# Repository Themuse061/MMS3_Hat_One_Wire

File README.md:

# MMS3 Hat One Wire

## Sekcja 0: Jak szybko, dobrze i tanio zrobić hata z dokumentacją

Szybka lista punkcików to wyklepania zanim hat magicznie się zrobi

1. **Sprawdź istniejące projekty:** Zobacz czy nie ma już jakiegoś hata który robi co potrzebujesz. Zobacz w forkach i poszukaj na githubie po hashtag'ach, jeśli nie to
2. **Utwórz Fork:** Kliknij przycisk **Fork** w prawym górnym rogu tego repozytorium.

1. **Konfiguracja repozytorium:** Daj mu adekwatną nazwe, i z'clone'uj forka do siebie na pc
2. **Zasady projektowania:**
   * Dokładniejsza dokumentacja znajduje się w Sekcji 2.
   * Do komunikacji możesz używać **wyłącznie** interfejsów: **I2C, SPI oraz UART**.
   * Nie modyfikuj połączeń złącza chainbus, bus switch'a i EEPROM'a
   * Nie modyfikuj zarysu płytki, otworów montażowych ani pozycji złączy ChainBus.
   * Możesz usunąć złącze XT60, jeśli Twój projekt go nie wymaga.

### Checklista przed zakończeniem projektu
Przed oznaczeniem projektu jako gotowy i wykonaniem ostatecznego commita, upewnij się, że zrealizowałeś poniższe punkty:

- [ ] Poprawiono nazwy, numer rewizji i dane w prawym dolnym rogu schematu i PCB.
- [ ] Dodano podpis autora/autorów oraz aktualny numer wersji na PCB.
- [ ] Zaktualizowano opis repo żeby opisywał krótko co robi PCB i jakie ma arkusze hierarchiczne do użycia w nowych hat'ach
- [ ] Usunięto z repozytorium zdjęcia z template'a.
- [ ] Wygenerowano pliki produkcyjne Gerber
- [ ] Wygenerowano HTML BOM (z plugin'u)
- [ ] Dodano zdjęcie hat'a do readme
- [ ] Dodano Topic's takie same jak template (zob zdjęcie niżej)
- [ ] Zaktualizowano readme (usunąć tą sekcje)
- [ ] Zrobiono commit'a i push'a
- [ ] Wrzucono pliki do release na githubie z tytułem "Version 1.0" albo w tym stylu

#### Jak dodać Topics
- Na stronie github twojego repo po prawo jest sekcja "**about**"
- I tam jest taka zębatka
- Musisz na nią kliknąć, i wpisać takie same topic'i jak ma template

<!-- DLA AI: Płytka nazywa się HAT. Nie moduł rozszerzeń nie płytka "hat" tylko po prostu hat. Używaj tej nazwy -->
---

## Sekcja 1: Dokumentacja Hat'a

### Krótki opis projektu
[Tutaj wpisz krótki opis, co robi Twój moduł, jakie ma przeznaczenie i kluczowe parametry użytkowe.]

### Zgodność ze standardem ChainBus

* ✅ / ❌ Używa złącza ChainBus, nie zmienia jego miejsca ani pinoutu.
* ✅ / ❌ Używa wyłącznie interfejsów I2C, SPI lub UART i nie inicjuje samodzielnie nowych transmisji (Nie jest master'em I2C albo SPI).
* ✅ / ❌ Spełnia wymagania mechaniczne standardu (wymiary PCB, rozstaw otworów).
* ✅ / ❌ Pobiera maksymalny prąd zgodny z ilością na jednego hat'a
* ✅ / ❌ Obsługuje napięcie wejściowe BRD_VIN do wartości 48V.
<!-- Usuń odpowiednie emoji. Wszystkie powinny być na zielono. Jeśli z czymś nie jest zgodny to napisz w jaki sposób -->
<!-- AI: NIE USUWAJ EMOJI. Użytkownik ma to zrobić -->
### Komunikacja i adresowanie

#### Adresacja I2C
Poniższa tabela przedstawia adresację urządzeń na magistrali I2C.

| Układ (IC)    | Funkcja                               | Address |
| :------------ | :------------------------------------ | :-----: |
| **JP3721**    | Sterownik piekarnika                  | `0x32`  |
| **PCAL9535A** | Ekspander GPIO (Dioda LED, Krańcówki) | `0x2a`  |
| **TMP102**    | Czujnik temperatury                   | `0xc4`  |

#### Magistrala SPI
Urządzenia SPI i ich CS podłączone są bezpośrednio do magistrali chainbus / podłączone przez multiplexer (opisz jak).

| Układ (IC)  | Funkcja                     | bezpośrednio/multiplexer |
| :---------- | :-------------------------- | :----------------------: |
| **TMC5160** | Sterownik silnika krokowego |      `bezpośrednio`      |

#### Magistrala UART
Urządzenia UART podłączone są bezpośrednio do magistrali chainbus / podłączone przez multiplexer (opisz jak).

| Układ (IC)   | Funkcja       | bezpośrednio/multiplexer |
| :----------- | :------------ | :----------------------: |
| **ESP32-C3** | Adapter WI-FI |      `bezpośrednio`      |

### Pinout złączy

| Jn     | Co                                         | Jaki pin co robi                                                     |
| :----- | :----------------------------------------- | :------------------------------------------------------------------- |
| **J1** | Zasilanie zewnętrzne silników              | Pin 1: VIN (zasilanie dodatnie)<br>Pin 2: GND (masa zasilania)       |
| **J2** | Wyjście faz silnika krokowego              | Pin 1: Faza A1<br>Pin 2: Faza A2<br>Pin 3: Faza B1<br>Pin 4: Faza B2 |
| **J3** | Wejście czujnika krańcowego (Limit Switch) | Pin 1: Sygnał wejściowy (z rezystorem Pull-Up)<br>Pin 2: GND (masa)  |

### Konfiguracja układu (Zworki/Rezystory)

| Co             | Jak podłączone | Efekt       |
| :------------- | :------------- | :---------- |
| **J1**         | 1-2 zwarte     | Silnik DC   |
|                | rozwarte       | Silnik BLDC |
| **J2**         | 1-2 zwarte     | 3.3V out    |
|                | 2-3 zwarte     | 5V out      |
| **R1, R2, R3** | Wlutowany R1   | 3.3V out    |
|                | Wlutowany R2   | 5V out      |
|                | Wlutowany R3   | VIN out     |

### Szczegółowy opis techniczny
[Tutaj umieść opis działania układu, parametry maksymalne etc]

### Gotowe arkusze hierarchiczne
W projekcie zaprojektowano/użyto następujących arkuszy hierarchicznych:
* [Nazwa arkusza 1] – [Krótki opis funkcjonalności, np. Zasilacz impulsowy 5V] - [ oryginalny/ wzięty z hata XXX]
* [Nazwa arkusza 2] – [Krótki opis] - [ -||- ]

---

## Sekcja 2: Specyfikacja standardu ChainBus

### Architektura i łączenie modułów
Standard ChainBus umożliwia modułowe łączenie hatów. Na jednym MMS3 można zamontować pionowo **do 8 hat'ów**. Połączenie realizowane jest poprzez wpięcie złącza męskiego kolejnego hat'a w złącze żeńskie poprzedniego

### Komunikacja i sterowanie
Magistrala ChainBus jest w pełni cyfrowa. Płyta główna nie steruje bezpośrednio sygnałami ogólnego przeznaczenia (GPIO) na poszczególnych hat'ach. Wszelkie operacje (np. obsługa diod LED, odczyt krańcówek, generowanie sygnałów PWM) muszą być realizowane przez dedykowane układy scalone (np. ekspandery portów, sterowniki) komunikujące się przez interfejsy systemowe.

*Przykład:*
`MCU` $\rightarrow$ `Expander GPIO po I2C` $\rightarrow$ `Dioda LED`

Wybór aktywnego modułu realizowany jest przez układ przełącznika magistrali (bus switch) na płycie głównej. Dzięki temu linie I2C, SPI i UART są niezależne dla każdego hat'a (brak konfliktów adresów I2C między różnymi hatami).
* **Identyfikacja:** Każdy moduł powinien posiadać pamięć EEPROM na magistrali I2C w celu identyfikacji płyty przez system - układ M24C64-W skonfigurowany na adres `0x50` przy liniach adresowych A0, A1, A2 zwartych do masy.

### Zasilanie
Złącze ChainBus dostarcza następujące linie zasilania:

| Magistrala zasilania | Napięcie znamionowe | Maksymalny prąd (łączny dla 8 hatów) | Szacowany prąd na jeden hat |
| :------------------- | :-----------------: | :----------------------------------: | :-------------------------: |
| **5V**               |        5.0 V        |                1.0 A                 |           125 mA            |
| **12V stby**         |       12.0 V        |                0.5 A                 |            65 mA            |
| **BRD_VIN**          |   12.0 V – 48.0 V   |                1.5 A                 |           185 mA            |

*   Komponenty podłączone do linii `BRD_VIN` muszą być przystosowane do pracy z napięciem od 12V do **48 V**.
*   W przypadku zapotrzebowania na wyższą moc, dopuszczalne jest zastosowanie dodatkowego złącza zasilania XT60 (obciążalność do ok. 60 A).

### Wymagania mechaniczne i złącza
* **Wymiary PCB:** Niedozwolona jest zmiana obrysu płytki oraz położenia otworów montażowych, aby zachować kompatybilność mechaniczną.
* **Pozycjonowanie złączy ChainBus:** Położenie złącza standardu 2x16 SMD (raster 2.54 mm) musi być zgodne z szablonem. Złącze żeńskie montowane jest na stronie FRONT, natomiast złącze męskie na stronie BACK.
* **Interfejsy zewnętrzne:** Złącza wejścia/wyjścia (domyślnie standard JST-XH 2.5 mm o obciążalności do 3 A) oraz opcjonalne złącze XT60 powinny być umieszczone przy dolnej krawędzi płytki. Elementy regulacyjne i sygnalizacyjne (potencjometry, przełączniki, diody LED) należy lokalizować przy prawej krawędzi płytki.
* **Komponenty** Wszystkie komponenty powinny być na stronie front płytki żeby nie haczyły o elementy ze wcześniejszego hat'a

---

## Sekcja 3: Licencje

### Licencje projektu

*   **PCB:** CERN-OHL-P
*   **Software:** MIT License

[Template](https://github.com/KoNaR-Hefajstos/MMS3_hat_templates/) jest na licencji CC0 1.0 Universal. **Reszta projektu nie jest na tej licencji**

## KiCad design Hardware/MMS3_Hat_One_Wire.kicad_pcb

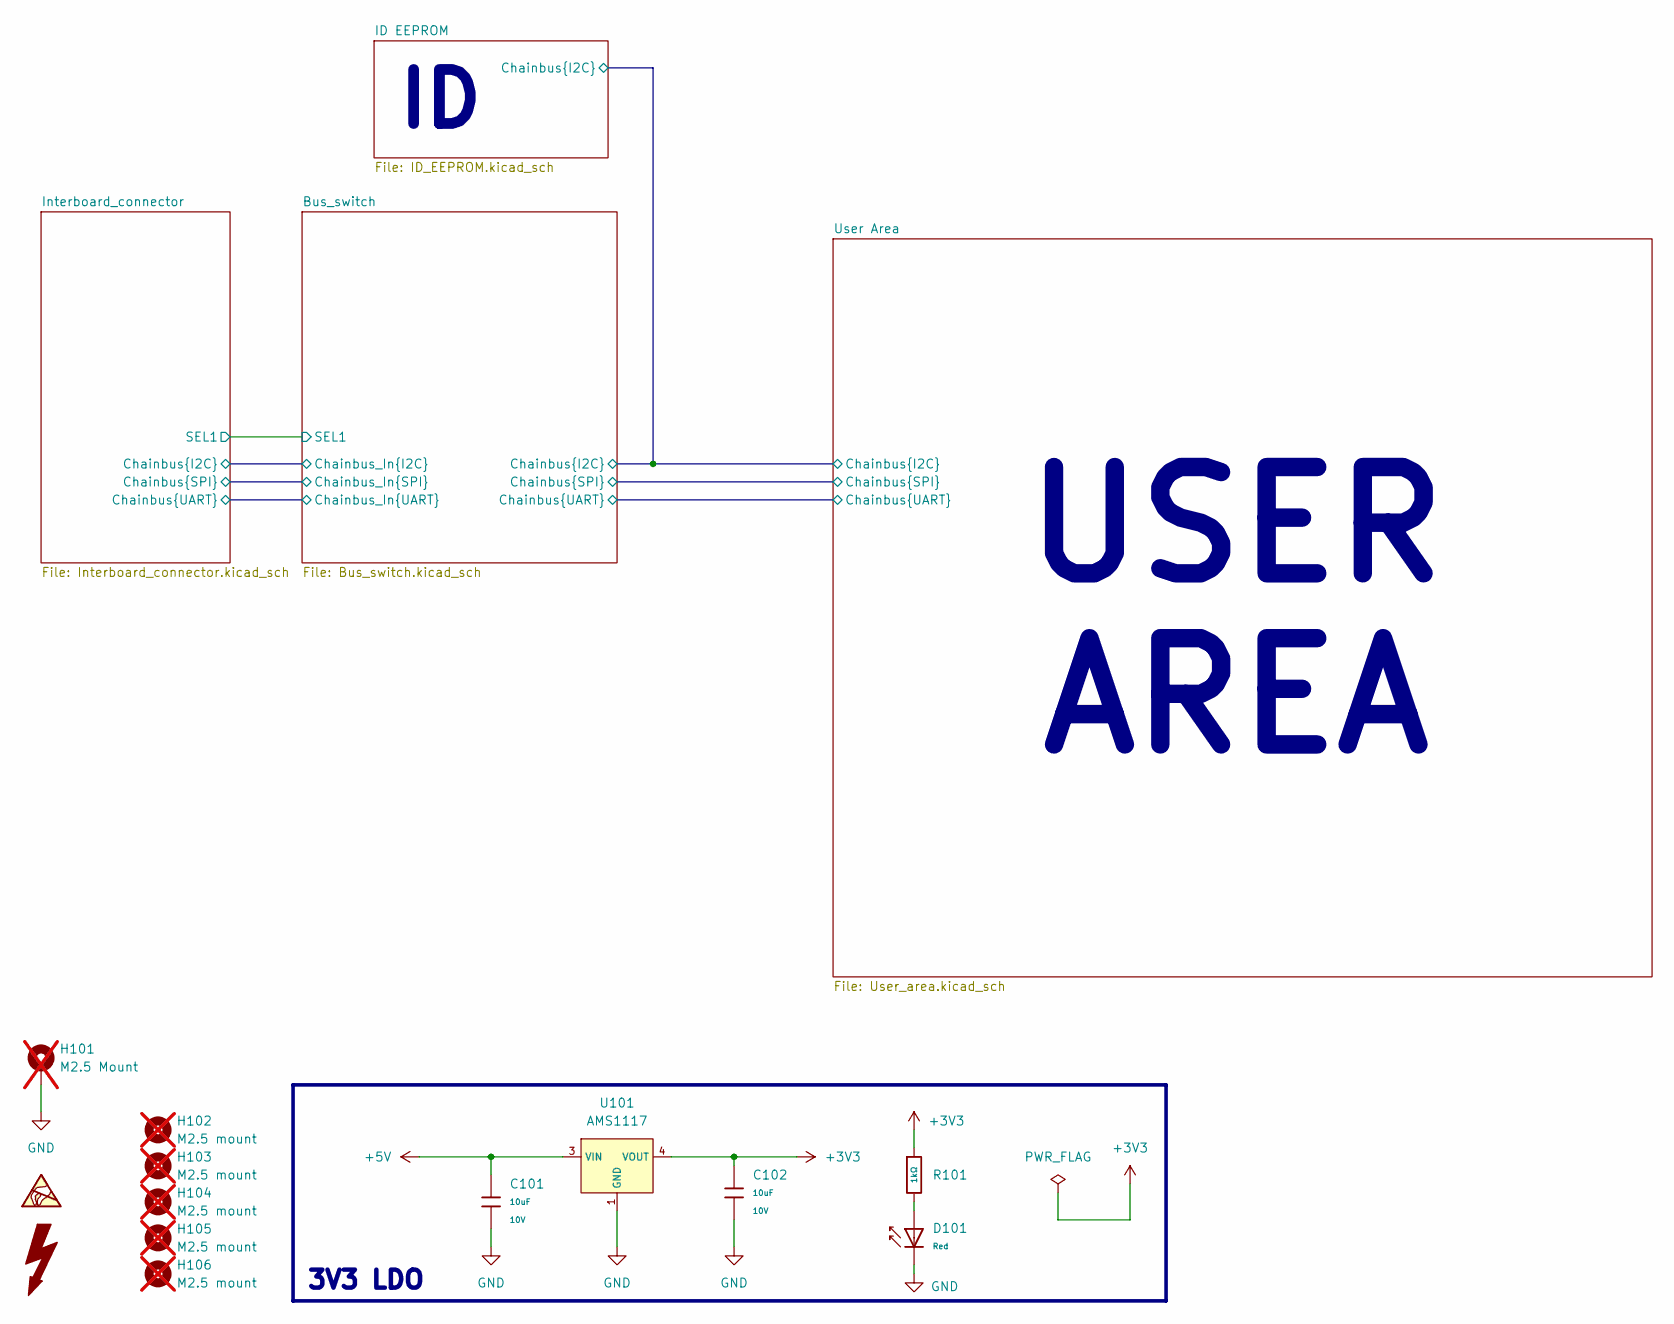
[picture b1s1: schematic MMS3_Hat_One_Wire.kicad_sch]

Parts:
C101, C102: 10uF; C_0603; Voltage Rated 10V; Tolerance ±10%; Part CL10A106KP8NNNC; LCSC C19702
D101: Red; D_0603; Part KT-0603R; LCSC C2286
H101: M2.5 Mount; MountingHole_2.7mm_M2.5_DIN965_Pad_TopOnly; not fitted
H102, H103, H104, H105, H106: M2.5 mount; MountingHole_2.7mm_M2.5; not fitted
R101: 1kΩ; R_0603; Overload Voltage (Max) 75V; Tolerance ±1%; Part 0603WAF1001T5E; LCSC C21190
U101: AMS1117; SOT-223-3_L6.5-W3.4-P2.30-LS7.0-BR; Output Voltage 3.3V; Dropout Voltage 1.3V@(800mA); Part AMS1117-3.3; LCSC C6186

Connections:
+3V3: C102.1, R101.1, U101.2 (VOUT), U101.4 (VOUT); also elsewhere on the board
+5V: C101.1, U101.3 (VIN); also elsewhere on the board
GND: C101.2, C102.2, D101.1, H101.1 (1_1), U101.1 (GND); also elsewhere on the board
unnamed: D101.2, R101.2

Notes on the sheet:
3V3 LDO
USER AREA

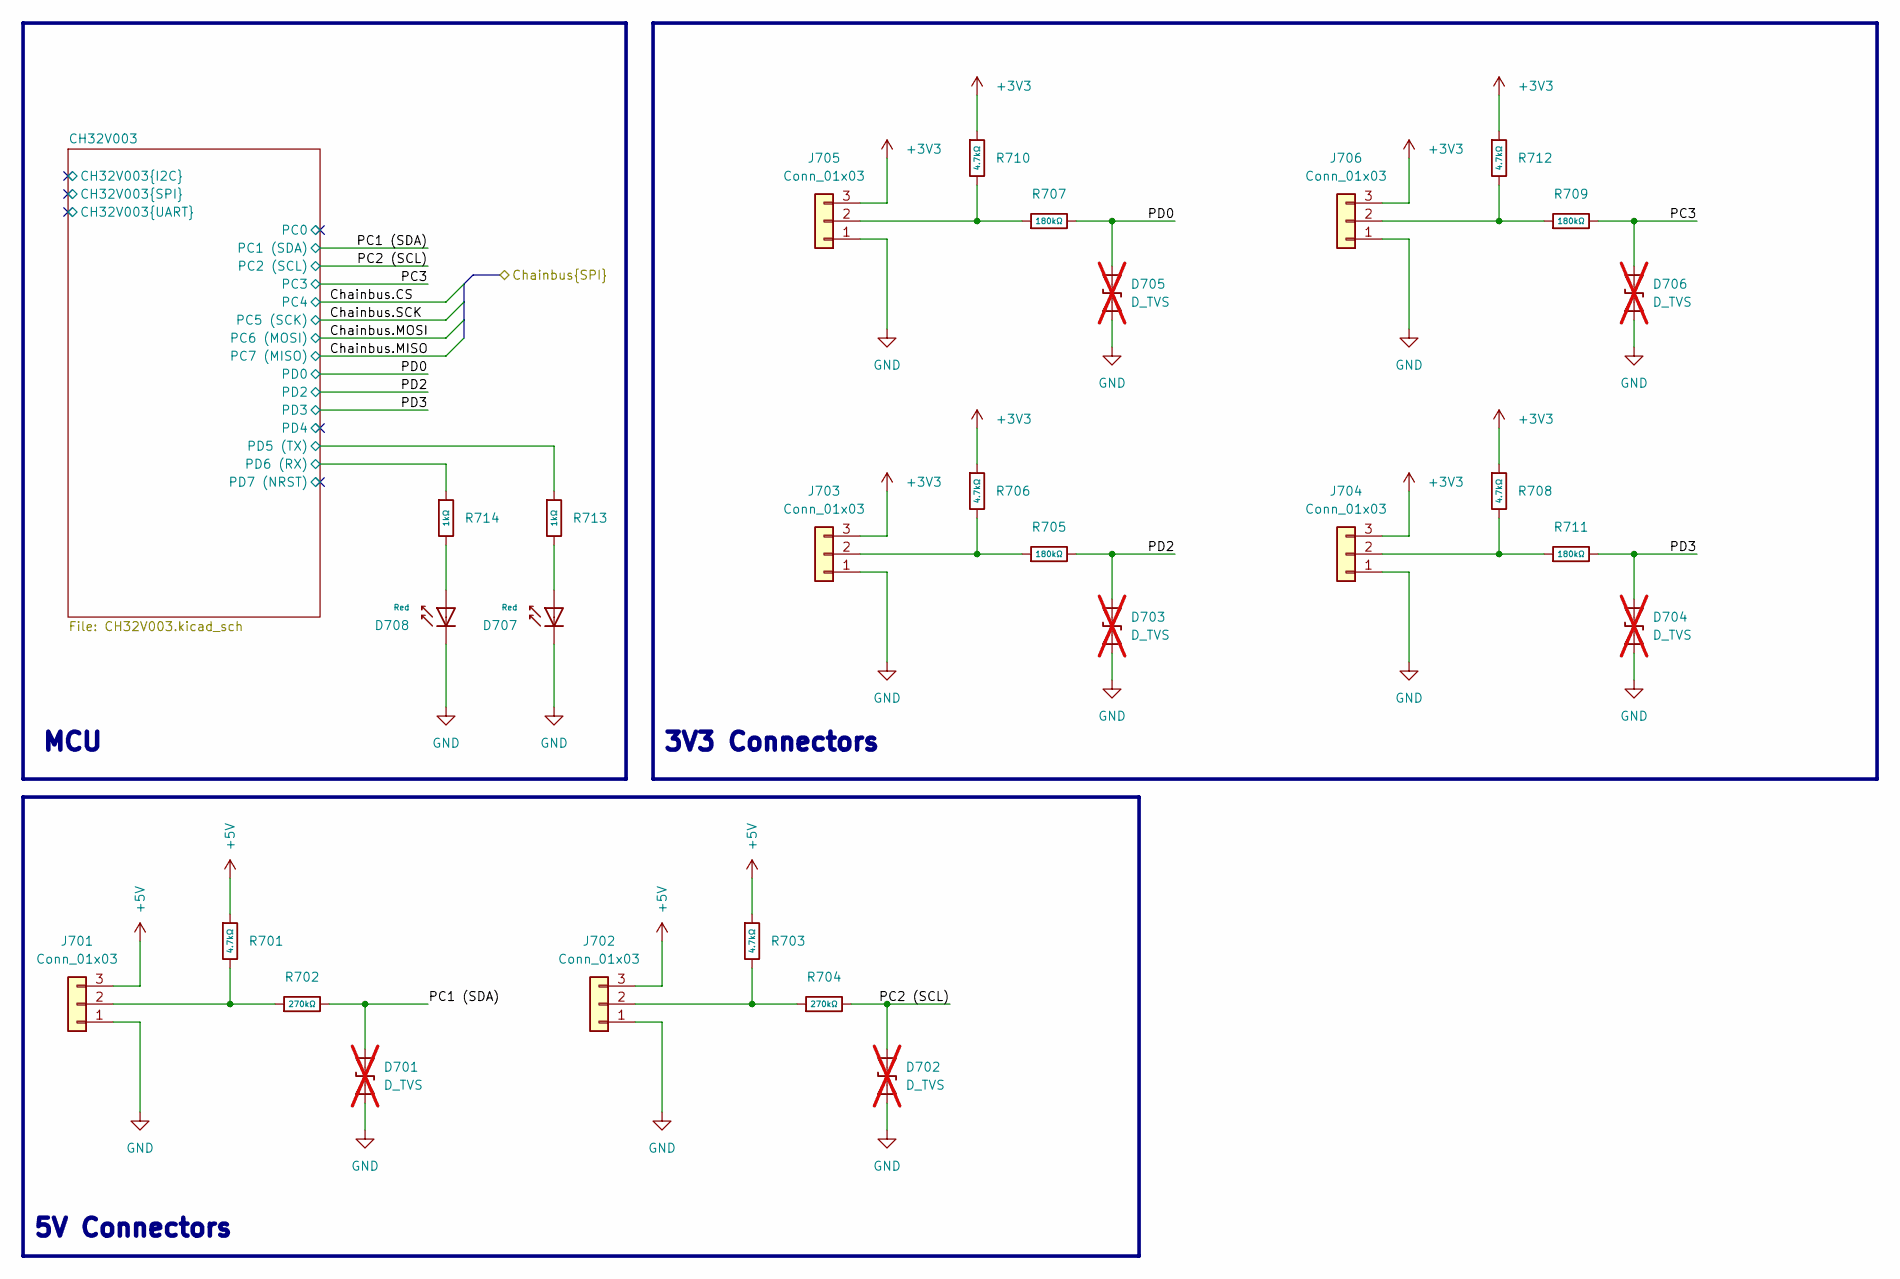
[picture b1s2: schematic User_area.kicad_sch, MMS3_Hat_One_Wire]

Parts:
D701, D702, D703, D704, D705, D706: D_TVS; D_0603_1608Metric; not fitted
D707, D708: Red; D_0603; Part KT-0603R; LCSC C2286
J701, J702, J703, J704, J705, J706: Conn_01x03; JST_XH_S3B-XH-A_1x03_P2.50mm_Horizontal
R701, R703, R706, R708, R710, R712: 4.7kΩ; R_0603; Overload Voltage (Max) 75V; Tolerance ±1%; Part 0603WAF4701T5E; LCSC C23162
R702, R704: 270kΩ; R_0603; Overload Voltage (Max) 75V; Tolerance ±1%; Part 0603WAF2703T5E; LCSC C22965
R705, R707, R709, R711: 180kΩ; R_0603; Overload Voltage (Max) 75V; Tolerance ±1%; Part 0603WAF1803T5E; LCSC C22827
R713, R714: 1kΩ; R_0603; Overload Voltage (Max) 75V; Tolerance ±1%; Part 0603WAF1001T5E; LCSC C21190

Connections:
+3V3: J703.3, J704.3, J705.3, J706.3, R706.1, R708.1, R710.1, R712.1; also elsewhere on the board
+5V: J701.3, J702.3, R701.1, R703.1; also elsewhere on the board
/User Area/CH32V003/CH32V003.RX: R714.1; also elsewhere on the board
/User Area/CH32V003/CH32V003.TX: R713.1; also elsewhere on the board
/User Area/PC1 (SDA): D701.2 (A2), R702.2; also elsewhere on the board
/User Area/PC2 (SCL): D702.2 (A2), R704.2; also elsewhere on the board
/User Area/PC3: D706.2 (A2), R709.2; also elsewhere on the board
/User Area/PD0: D705.2 (A2), R707.2; also elsewhere on the board
/User Area/PD2: D703.2 (A2), R705.2; also elsewhere on the board
/User Area/PD3: D704.2 (A2), R711.2; also elsewhere on the board
GND: D701.1 (A1), D702.1 (A1), D703.1 (A1), D704.1 (A1), D705.1 (A1), D706.1 (A1), D707.1, D708.1, J701.1, J702.1, J703.1, J704.1, J705.1, J706.1; also elsewhere on the board
unnamed: D707.2, R713.2
unnamed: D708.2, R714.2
unnamed: J701.2, R701.2, R702.1
unnamed: J702.2, R703.2, R704.1
unnamed: J703.2, R705.1, R706.2
unnamed: J704.2, R708.2, R711.1
unnamed: J705.2, R707.1, R710.2
unnamed: J706.2, R709.1, R712.2

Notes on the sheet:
MCU
3V3 Connectors
5V Connectors

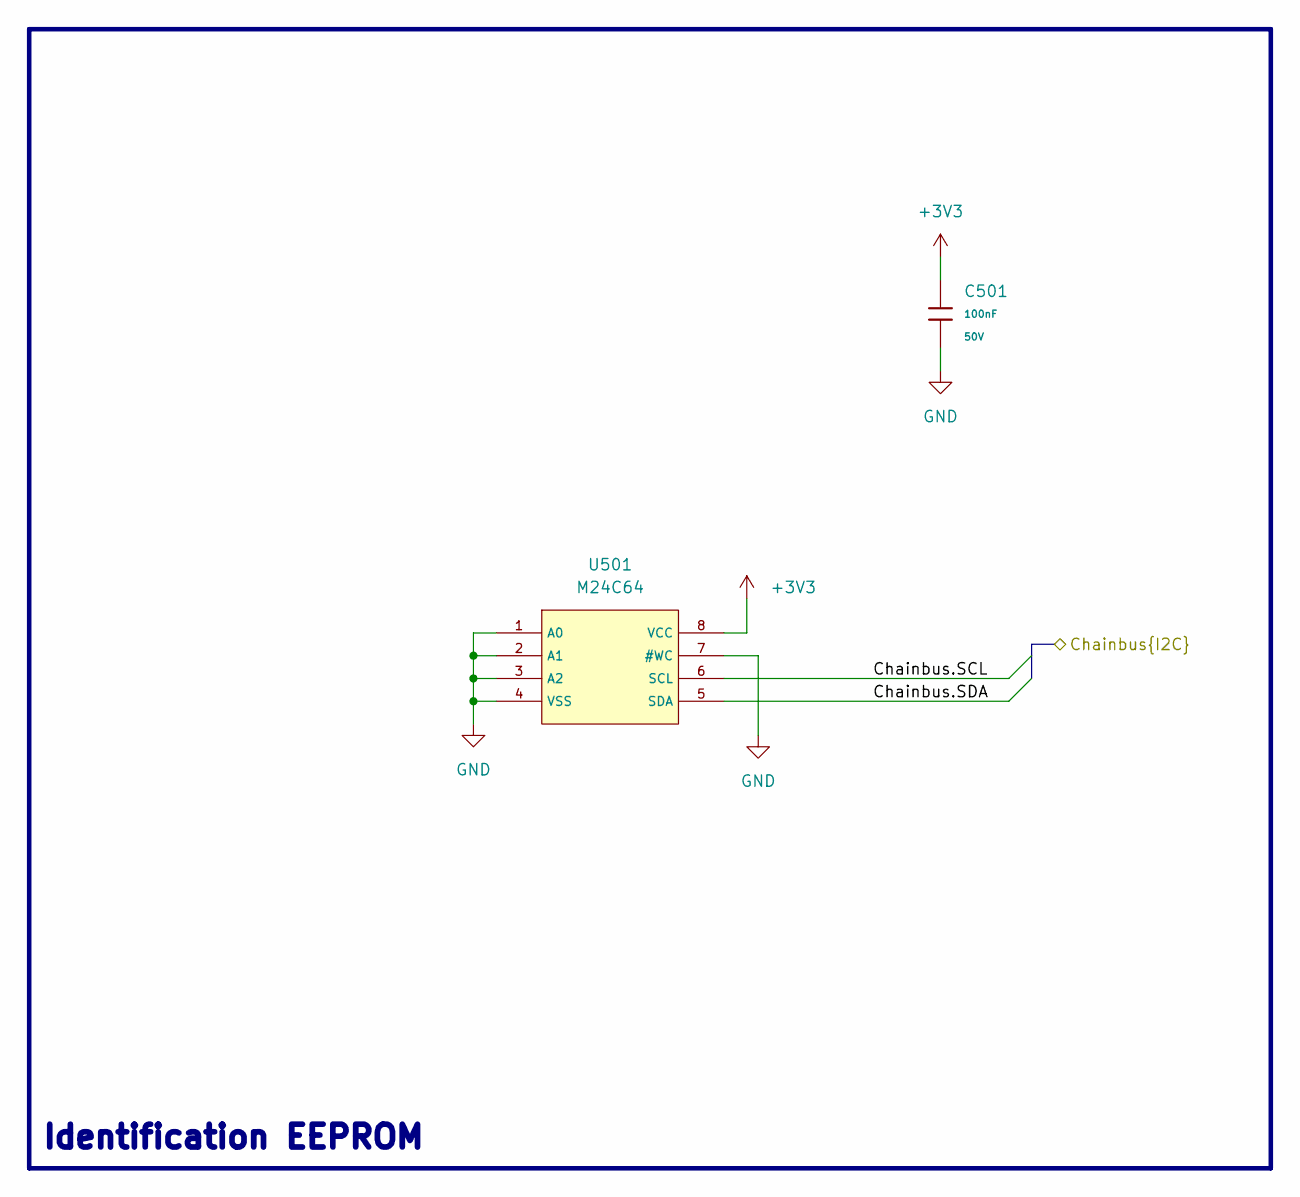
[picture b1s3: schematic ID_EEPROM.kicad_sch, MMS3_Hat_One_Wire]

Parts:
C501: 100nF; C_0603; Voltage Rated 50V; Tolerance ±10%; Part CC0603KRX7R9BB104; LCSC C14663
U501: M24C64; SOIC-8_L5.0-W4.0-P1.27-LS6.0-BL; Supply Voltage 1.8V~5.5V; Part M24C64-RMN6TP; LCSC C79988

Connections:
+3V3: C501.1, U501.8 (VCC); also elsewhere on the board
/Bus_switch/Chainbus.SCL: U501.6 (SCL); also elsewhere on the board
/Bus_switch/Chainbus.SDA: U501.5 (SDA); also elsewhere on the board
GND: C501.2, U501.1 (A0), U501.2 (A1), U501.3 (A2), U501.4 (VSS), U501.7 (#WC); also elsewhere on the board

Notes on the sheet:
Identification EEPROM

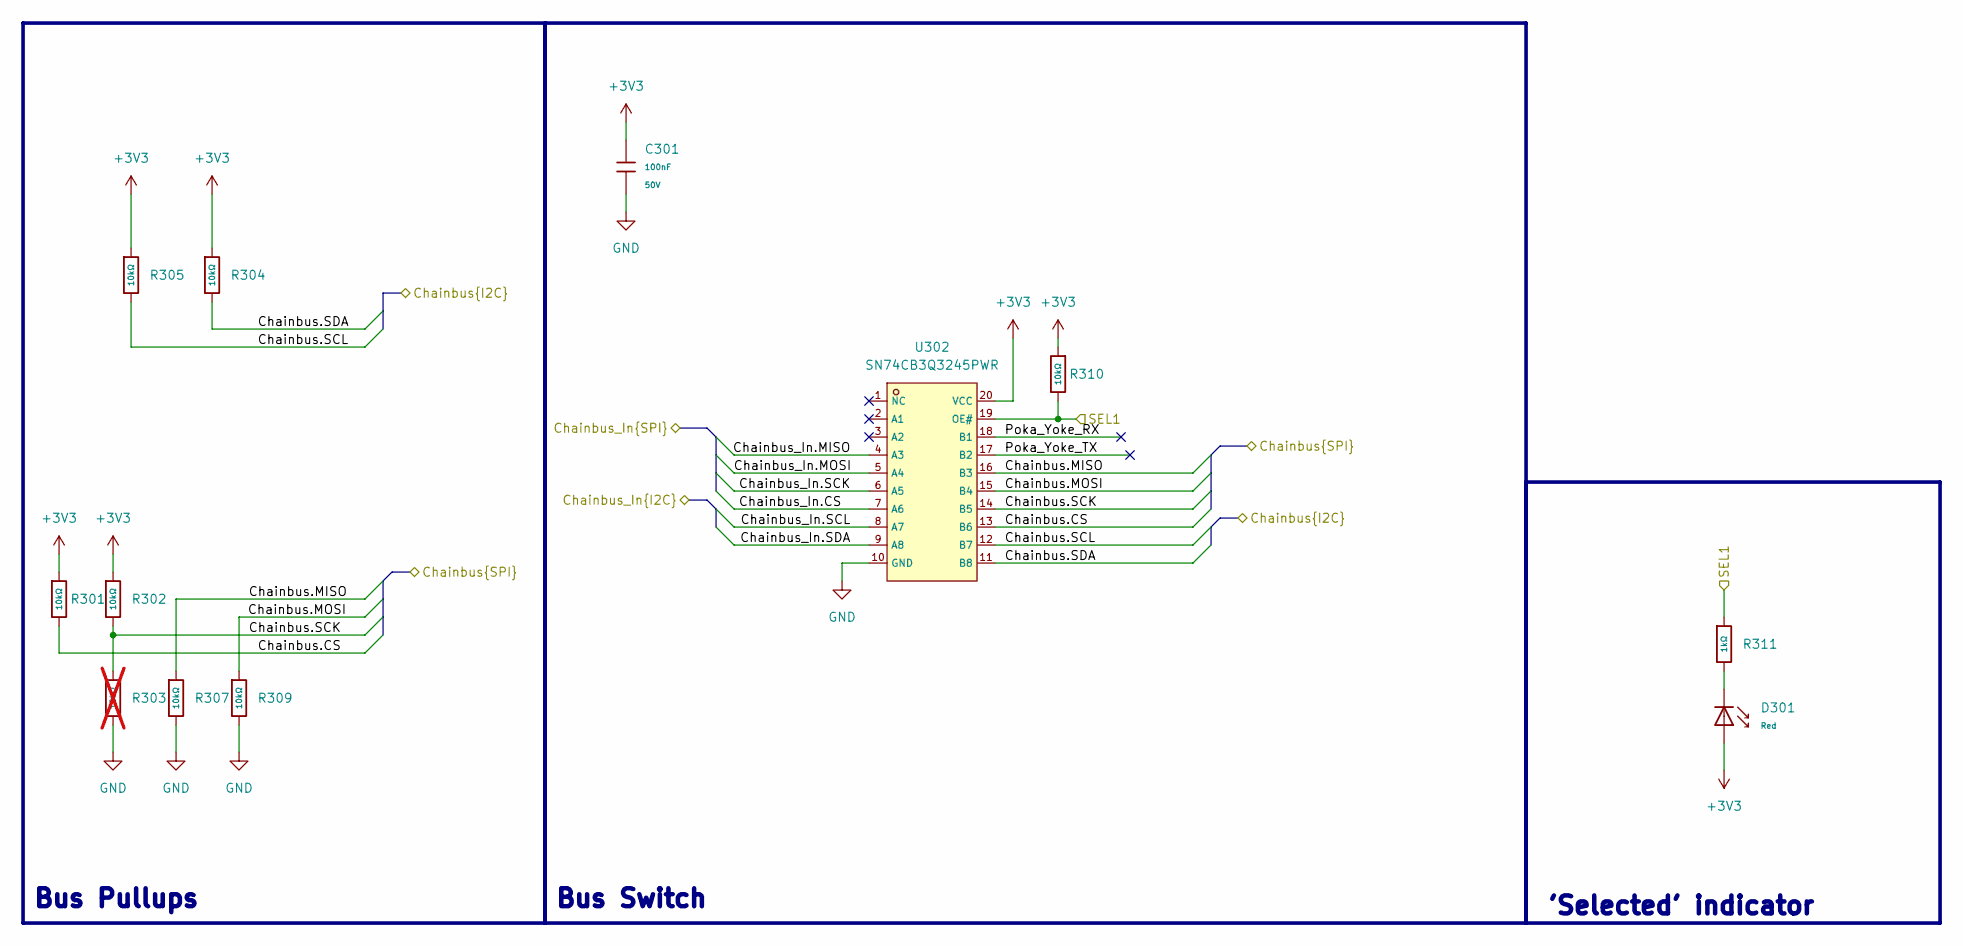
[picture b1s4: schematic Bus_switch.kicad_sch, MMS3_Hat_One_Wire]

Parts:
C301: 100nF; C_0603; Voltage Rated 50V; Tolerance ±10%; Part CC0603KRX7R9BB104; LCSC C14663
D301: Red; D_0603; Part KT-0603R; LCSC C2286
R301, R302, R304, R305, R307, R309, R310: 10kΩ; R_0603; Overload Voltage (Max) 75V; Tolerance ±1%; Part 0603WAF1002T5E; LCSC C25804
R303: 10kΩ; R_0603; Overload Voltage (Max) 75V; Tolerance ±1%; Part 0603WAF1002T5E; LCSC C25804; not fitted
R311: 1kΩ; R_0603; Overload Voltage (Max) 75V; Tolerance ±1%; Part 0603WAF1001T5E; LCSC C21190
U302: SN74CB3Q3245PWR; C470961_TSSOP-20_L6_5-W4_4-P0_65-LS6_4-BL; LCSC C470961

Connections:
+3V3: C301.1, D301.2, R301.1, R302.1, R304.1, R305.1, R310.1, U302.20 (VCC); also elsewhere on the board
/Bus_switch/Chainbus.CS: R301.2, U302.13 (B6); also elsewhere on the board
/Bus_switch/Chainbus.MISO: R307.1, U302.16 (B3); also elsewhere on the board
/Bus_switch/Chainbus.MOSI: R309.1, U302.15 (B4); also elsewhere on the board
/Bus_switch/Chainbus.SCK: R302.2, R303.1, U302.14 (B5); also elsewhere on the board
/Bus_switch/Chainbus.SCL: R305.2, U302.12 (B7); also elsewhere on the board
/Bus_switch/Chainbus.SDA: R304.2, U302.11 (B8); also elsewhere on the board
/Bus_switch/Chainbus_In.CS: U302.7 (A6); also elsewhere on the board
/Bus_switch/Chainbus_In.MISO: U302.4 (A3); also elsewhere on the board
/Bus_switch/Chainbus_In.MOSI: U302.5 (A4); also elsewhere on the board
/Bus_switch/Chainbus_In.SCK: U302.6 (A5); also elsewhere on the board
/Bus_switch/Chainbus_In.SCL: U302.8 (A7); also elsewhere on the board
/Bus_switch/Chainbus_In.SDA: U302.9 (A8); also elsewhere on the board
/Bus_switch/Poka_Yoke_RX: U302.18 (B1)
/Bus_switch/Poka_Yoke_TX: U302.17 (B2)
/Bus_switch/SEL1: R310.2, R311.1, U302.19 (OE#); also elsewhere on the board
GND: C301.2, R303.2, R307.2, R309.2, U302.10 (GND); also elsewhere on the board
unnamed: D301.1, R311.2

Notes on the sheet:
Bus Switch
Bus Pullups
'Selected' indicator

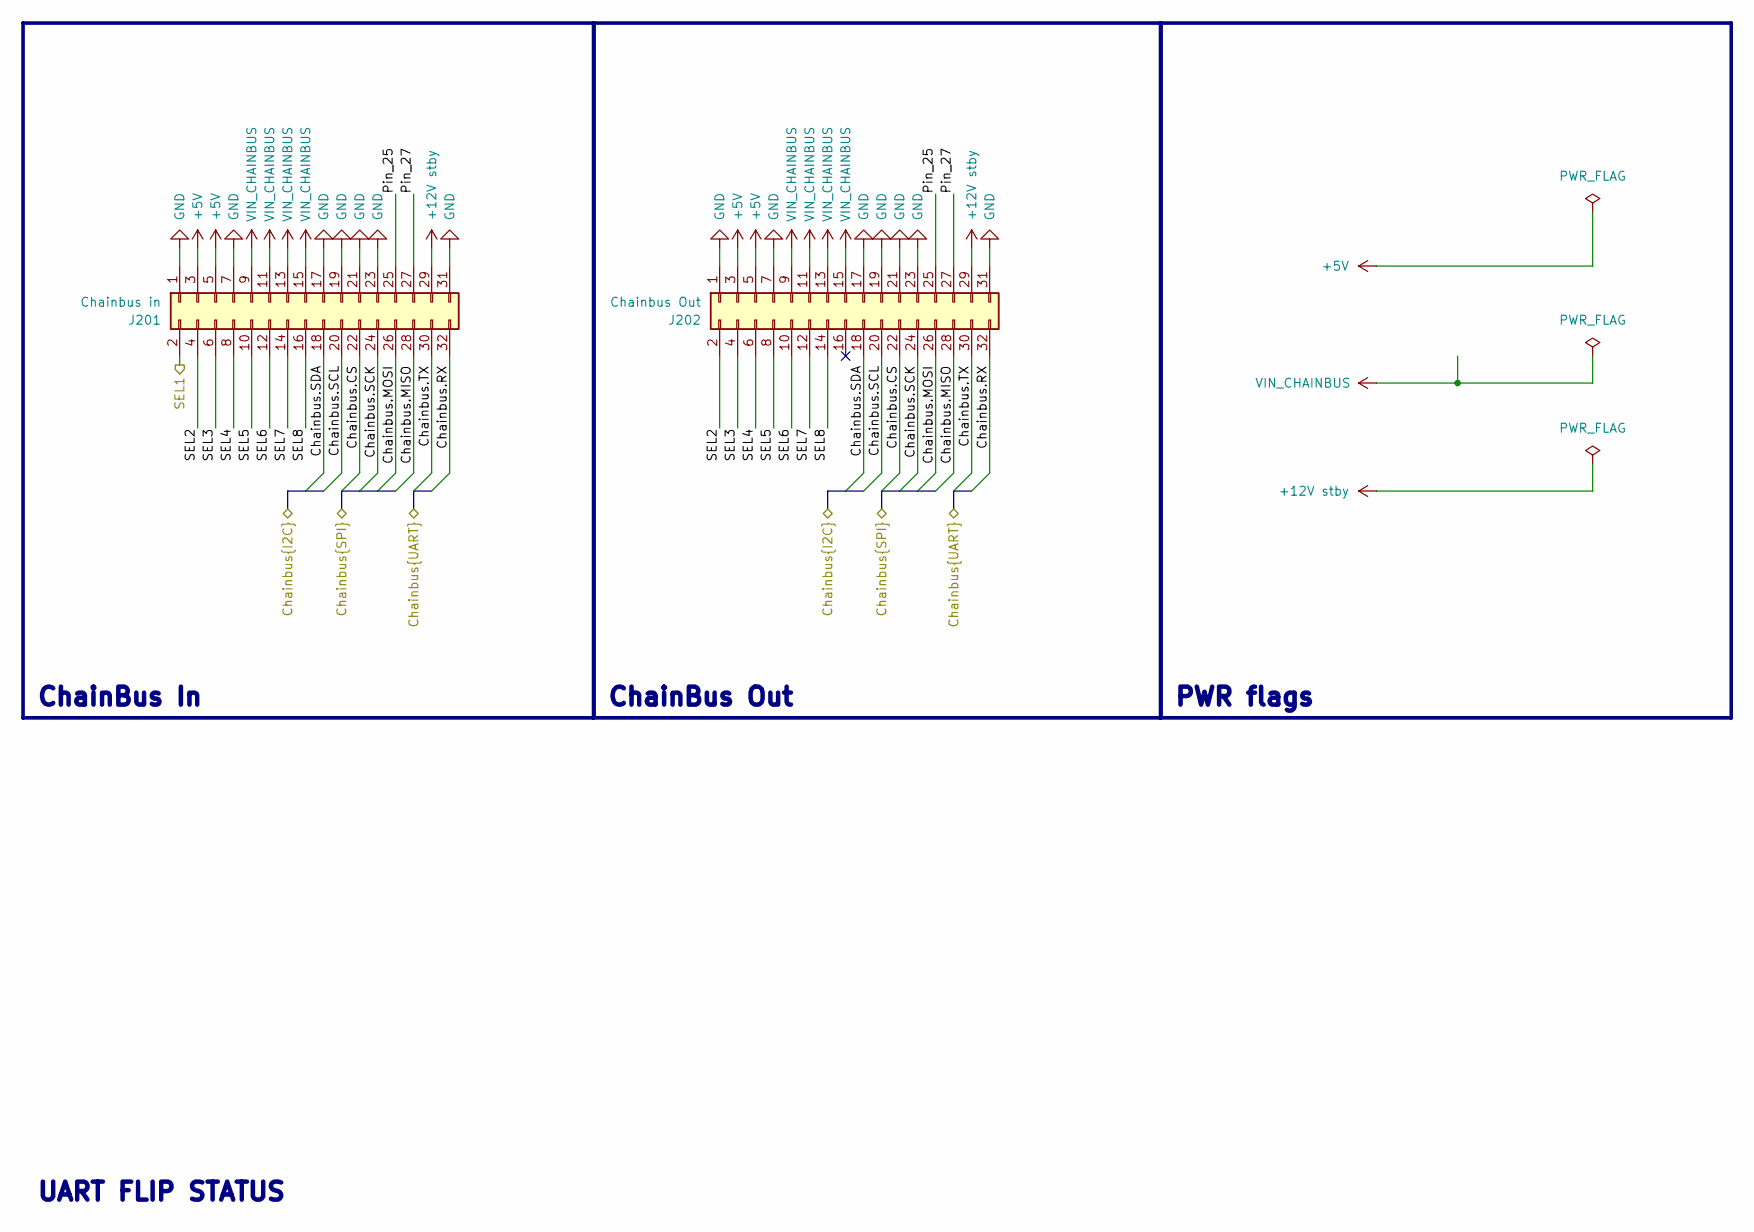
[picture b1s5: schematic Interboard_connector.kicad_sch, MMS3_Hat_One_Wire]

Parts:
J201: Chainbus in; PinHeader_2x16_P2.54mm_Vertical_SMD
J202: Chainbus Out; PinSocket_2x16_P2.54mm_Vertical_SMD

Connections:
+5V: J201.3, J201.5, J202.3, J202.5; also elsewhere on the board
+12V stby: J201.29, J202.29
/Bus_switch/Chainbus_In.CS: J201.22, J202.22; also elsewhere on the board
/Bus_switch/Chainbus_In.MISO: J201.28, J202.28; also elsewhere on the board
/Bus_switch/Chainbus_In.MOSI: J201.26, J202.26; also elsewhere on the board
/Bus_switch/Chainbus_In.SCK: J201.24, J202.24; also elsewhere on the board
/Bus_switch/Chainbus_In.SCL: J201.20, J202.20; also elsewhere on the board
/Bus_switch/Chainbus_In.SDA: J201.18, J202.18; also elsewhere on the board
/Bus_switch/SEL1: J201.2; also elsewhere on the board
/Interboard_connector/Chainbus.RX: J201.32, J202.32
/Interboard_connector/Chainbus.TX: J201.30, J202.30
/Interboard_connector/Pin_25: J201.25, J202.25
/Interboard_connector/Pin_27: J201.27, J202.27
/Interboard_connector/SEL2: J201.4, J202.2
/Interboard_connector/SEL3: J201.6, J202.4
/Interboard_connector/SEL4: J201.8, J202.6
/Interboard_connector/SEL5: J201.10, J202.8
/Interboard_connector/SEL6: J201.12, J202.10
/Interboard_connector/SEL7: J201.14, J202.12
/Interboard_connector/SEL8: J201.16, J202.14
GND: J201.1, J201.7, J201.17, J201.19, J201.21, J201.23, J201.31, J202.1, J202.7, J202.17, J202.19, J202.21, J202.23, J202.31; also elsewhere on the board
VIN_CHAINBUS: J201.9, J201.11, J201.13, J201.15, J202.9, J202.11, J202.13, J202.15

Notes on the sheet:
ChainBus In
UART FLIP STATUS
PWR flags
ChainBus Out

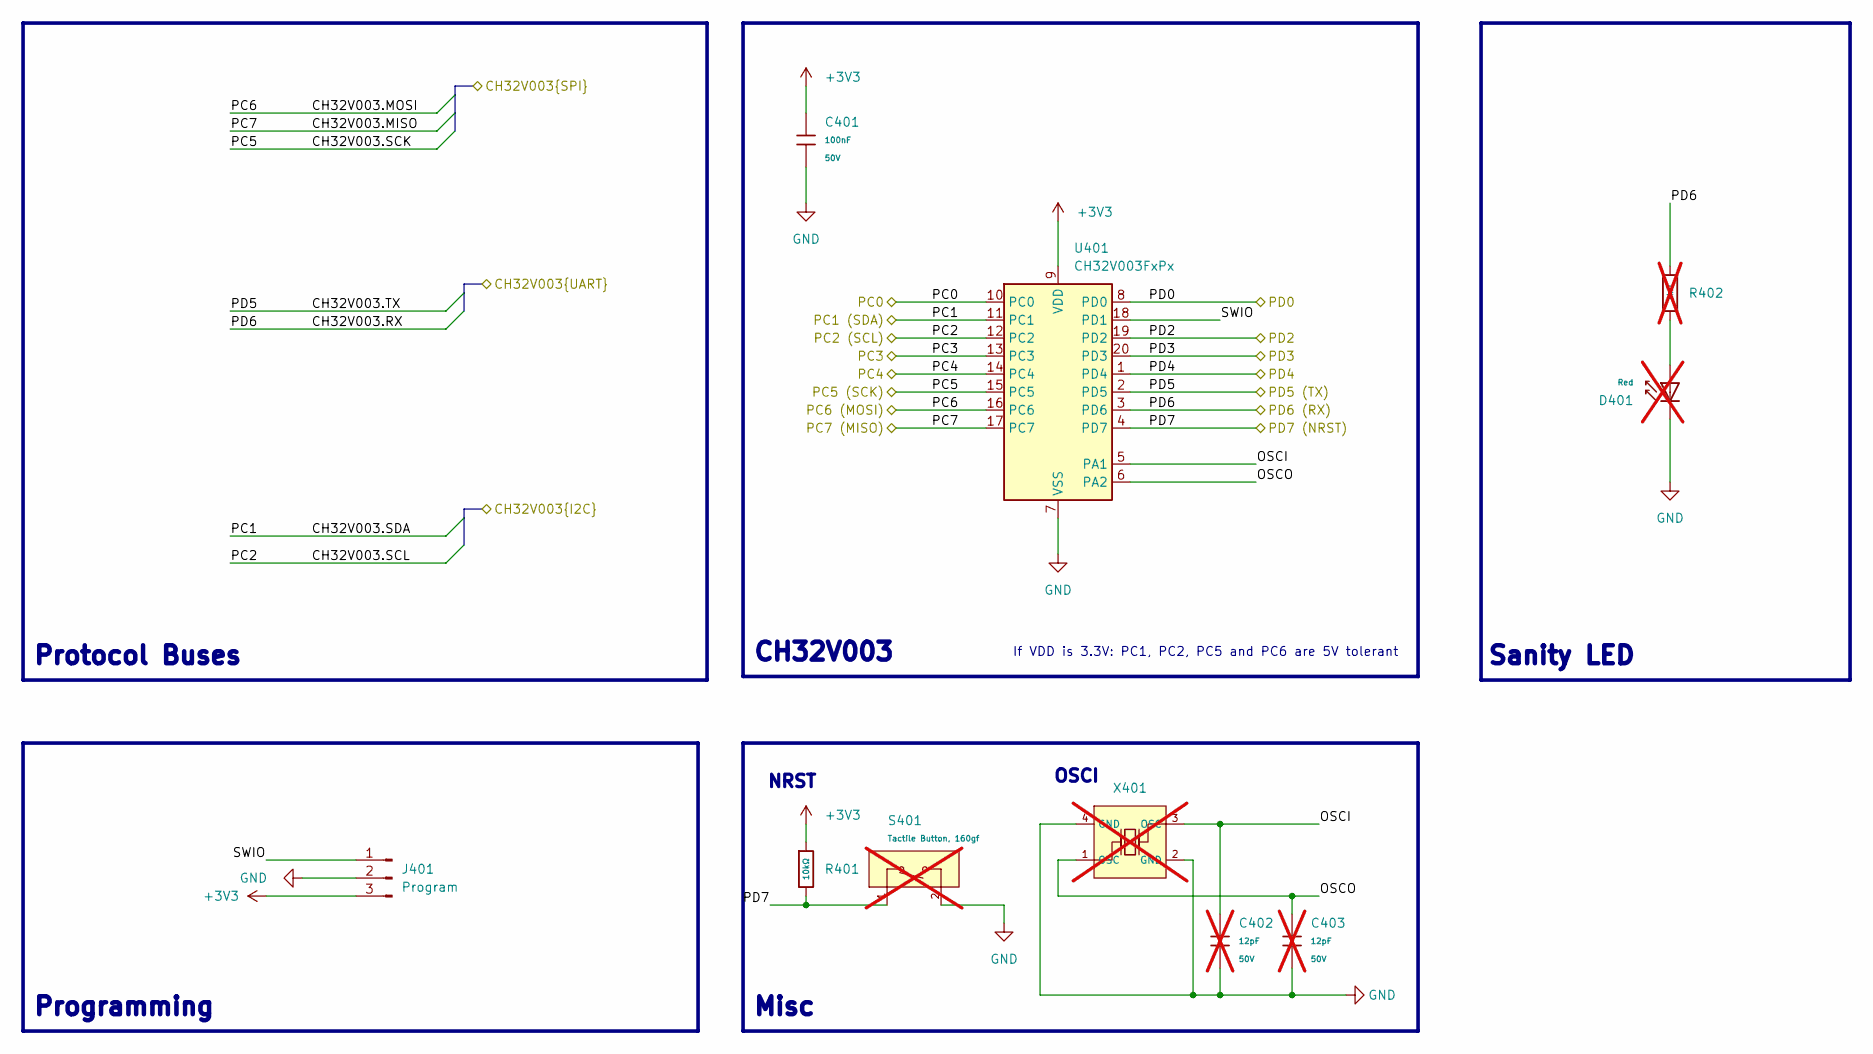
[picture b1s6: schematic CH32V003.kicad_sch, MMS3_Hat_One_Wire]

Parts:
C401: 100nF; C_0603; Voltage Rated 50V; Tolerance ±10%; Part CC0603KRX7R9BB104; LCSC C14663
C402, C403: 12pF; C_0603; Voltage Rated 50V; Tolerance ±5%; Part CL10C120JB8NNNC; LCSC C38523; not fitted
D401: Red; D_0603; Part KT-0603R; LCSC C2286; not fitted
J401: Program; JST_XH_B3B-XH-A_1x03_P2.50mm_Vertical
R401: 10kΩ; R_0603; Overload Voltage (Max) 75V; Tolerance ±1%; Part 0603WAF1002T5E; LCSC C25804
R402: 1kΩ; R_0603; Overload Voltage (Max) 75V; Tolerance ±1%; Part 0603WAF1001T5E; LCSC C21190; not fitted
S401: Tactile Button, 160gf; SW_TS-1088-AR02016; Voltage Rating (Dc) 12V; Part TS-1088-AR02016; LCSC C720477; not fitted
U401: CH32V003FxPx; TSSOP-20_4.4x6.5mm_P0.65mm
X401: X322525MOB4SI; OSC-SMD_4P-L3.2-W2.5-BL; Frequency Tolerance ±10ppm; Part X322525MOB4SI; LCSC C9006; not fitted

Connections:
+3V3: C401.1, J401.3, R401.1, U401.9 (VDD); also elsewhere on the board
/Bus_switch/Chainbus.CS: U401.14 (PC4); also elsewhere on the board
/Bus_switch/Chainbus.MISO: U401.17 (PC7); also elsewhere on the board
/Bus_switch/Chainbus.MOSI: U401.16 (PC6); also elsewhere on the board
/Bus_switch/Chainbus.SCK: U401.15 (PC5); also elsewhere on the board
/User Area/CH32V003/CH32V003.RX: R402.1, U401.3 (PD6); also elsewhere on the board
/User Area/CH32V003/CH32V003.TX: U401.2 (PD5); also elsewhere on the board
/User Area/CH32V003/OSCI: C402.1, U401.5 (PA1), X401.3 (OSC)
/User Area/CH32V003/OSCO: C403.1, U401.6 (PA2), X401.1 (OSC)
/User Area/CH32V003/PC0: U401.10 (PC0)
/User Area/CH32V003/PD4: U401.1 (PD4)
/User Area/CH32V003/PD7: R401.2, S401.1 (A), U401.4 (PD7)
/User Area/CH32V003/SWIO: J401.1, U401.18 (PD1)
/User Area/PC1 (SDA): U401.11 (PC1); also elsewhere on the board
/User Area/PC2 (SCL): U401.12 (PC2); also elsewhere on the board
/User Area/PC3: U401.13 (PC3); also elsewhere on the board
/User Area/PD0: U401.8 (PD0); also elsewhere on the board
/User Area/PD2: U401.19 (PD2); also elsewhere on the board
/User Area/PD3: U401.20 (PD3); also elsewhere on the board
GND: C401.2, C402.2, C403.2, D401.1, J401.2, S401.2 (B), U401.7 (VSS), X401.2 (GND), X401.4 (GND); also elsewhere on the board
unnamed: D401.2, R402.2

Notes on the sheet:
NRST
Sanity LED
If VDD is 3.3V: PC1, PC2, PC5 and PC6 are 5V tolerant
CH32V003
OSCI
Protocol Buses
Misc
Programming

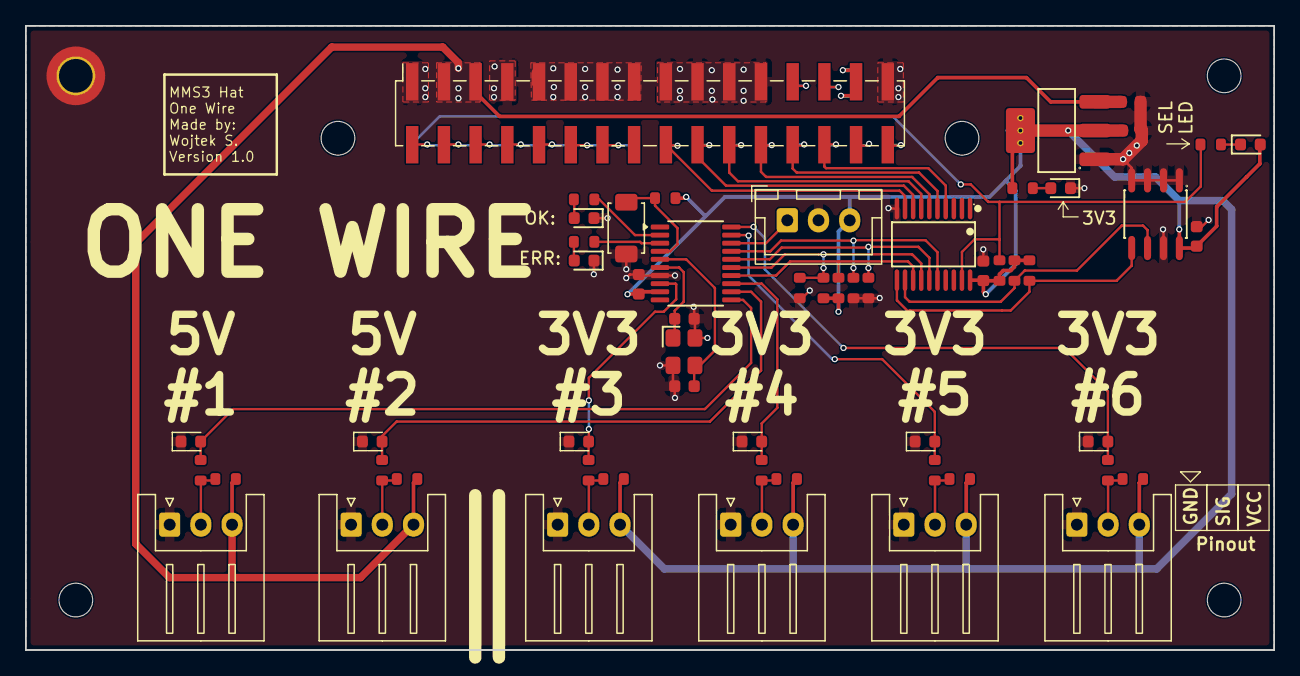
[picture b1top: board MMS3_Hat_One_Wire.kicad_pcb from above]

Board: 2 copper layers, 100.0 x 50.0 mm, 63 parts (1 on the bottom side), 51 nets.
